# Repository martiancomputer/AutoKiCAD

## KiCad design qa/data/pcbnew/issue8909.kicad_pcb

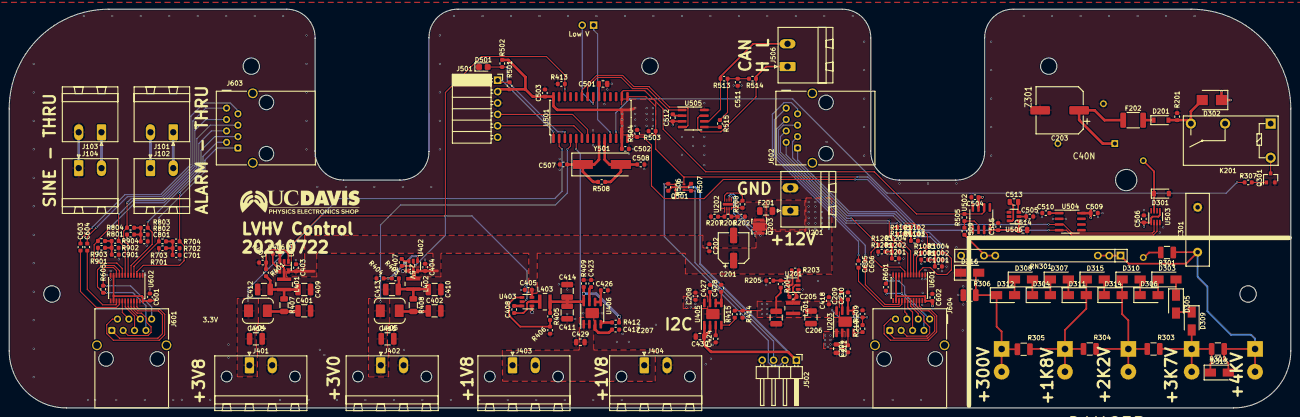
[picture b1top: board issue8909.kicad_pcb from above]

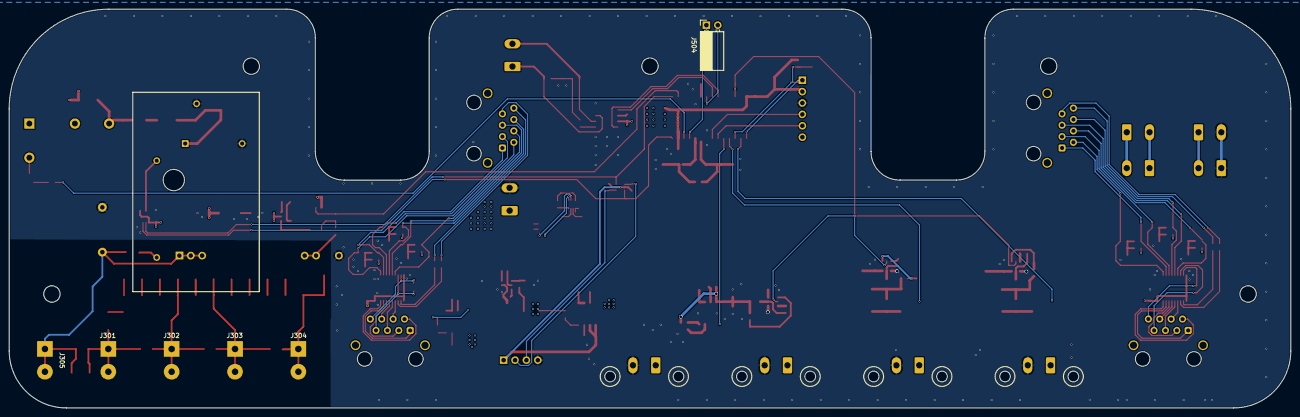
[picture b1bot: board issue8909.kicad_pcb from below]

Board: 4 copper layers, 285.8 x 88.9 mm, 204 parts (7 on the bottom side), 138 nets.

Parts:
C201: 10uF; CP_Elec_6.3x5.9
C202, C205, C208, C403, C404, C405, C406, C407, C408, C418, C502, C503, C504, C505, C506, C509, C510, C511, C512, C515, C601, C602, C603, C604, C605, C606, C701, C801, C901, C1001, C1101, C1201: 0u1F; C_0603_1608Metric
C203: 150uF; CP_Elec_10x7.7
C204, C209, C210, C417, C423, C424, C426, C427, C428: 1uF; C_0603_1608Metric
C206, C207, C409, C410, C411, C412, C413, C414: 22uF; C_1210_3225Metric
C211, C429, C430, C501, C513, C514: 10uF; C_0805_2012Metric
C301: 2nF; C_Disc_D16.0mm_W5.0mm_P10.00mm
C401, C402, C415, C416: 47uF; C_1210_3225Metric
C507, C508: 20pF; C_0603_1608Metric
D201, D301: 1N5819; D_SOD-123
D302: S1KB-13-F; D_SMB
D303, D304, D305, D306, D307, D308, D309, D310, D311, D312: 200V; D_SMA
D313, D314, D315, D316: 75V; D_SMA
D501: D_Photo; D_0805_2012Metric_Castellated
Davis_Shop_25mm: LOGO***; Davis_Shop_25mm
F201: Fuse; Fuse_1206_3216Metric
F202: Polyfuse; Fuse_1812_4532Metric_Pad1.30x3.40mm_HandSolder
J101, J102, J103, J104, J201: Conn_01x02_Male; PhoenixContact_MSTBA_2,5_2-G-5,08_1x02_P5.08mm_Horizontal
J301, J302, J303, J304, J305: Conn_01x01_Male; TE_63951-1_1x02_P5.08mm_Drill1.45mm
J401, J402, J403, J404: Conn_01x03; PhoenixContact_MSTB_2,5_2-GF-5,08_1x02_P5.08mm_Horizontal_T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
J501: Conn_01x06_Female; PinSocket_1x06_P2.54mm_Horizontal
J502: 61900419521; PinHeader_1x04_P2.54mm_Horizontal
J504: Conn_01x04; PinSocket_1x02_P2.54mm_Horizontal
J506: Conn_01x02; PhoenixContact_MSTBA_2,5_2-G-5,08_1x02_P5.08mm_Horizontal
J601, J602, J603, J604: RJ45; RJ45_Wuerth_615008142621_Horizontal
K201: G5Q-1A4 DC12; Relay_SPST_Omron-G5Q-1A
L201, L401, L402, L403: 3u3H; L_Pulse_PA4331.332NLT
L404, L405: 200nH; L_Bourns_SRP5015
Q203: CSD87312Q3E; Texas_CSD87312Q3E
Q301: MMBTA42; SOT-23
Q501: DMN601DWK-7; SOT-363_SC-70-6
R201, R203, R208, R209, R210, R409, R412, R414, R415: 100k; R_0603_1608Metric
R202: 1M33; R_0603_1608Metric
R204: 54k9; C_0603_1608Metric
R205, R402, R404, R406, R413, R501, R502, R505, R509, R701, R801, R901, R1001, R1101, R1201: 10k; R_0603_1608Metric
R206: 20k; R_0603_1608Metric
R207: 42k; R_0603_1608Metric
R301: 100R; R_1210_3225Metric
R302, R304, R306: 2M; R_1210_3225Metric
R303, R305: 10M; R_1210_3225Metric
R307: 1k; R_0603_1608Metric
R401: 39k; C_0603_1608Metric
R403: 29k; C_0603_1608Metric
R405: 24k9; R_0603_1608Metric
R407, R408: 0R2; R_1206_3216Metric
R503, R504, R506, R507: 2k; R_0603_1608Metric
R508: 1M; R_0603_1608Metric
R513, R514: 60R4; C_0603_1608Metric
R515: 300R; C_0603_1608Metric
R601, R605: 100R; R_0603_1608Metric
R702, R802, R902, R1002, R1102, R1202: 5k7; R_0603_1608Metric
R703, R704, R803, R804, R903, R904, R1003, R1004, R1103, R1104, R1203, R1204: 49R9; R_0603_1608Metric
RN301: HVD5-A50M; Caddock_USVD_HVD
U201, U401, U402, U403: TPS562200; SOT-23-6
U202: LTC4365IDDB; DFN-8-1EP_2x3mm_P0.5mm_EP0.61x2.2mm
U203, U405: ADP7158ARDZ-3.3; SOIC-8-1EP_3.9x4.9mm_P1.27mm_EP2.29x3mm
U406: ADP7158ARDZ-1.8; SOIC-8-1EP_3.9x4.9mm_P1.27mm_EP2.29x3mm
U501: DSPIC33EV256GM102; SOIC-28W_7.5x17.9mm_P1.27mm
U502: OPA196IDR; SOIC-8_3.9x4.9mm_P1.27mm
U503: LTC2631-HZ; TSOT-23-8
U504: HIH6030-21; SOIC-8_3.9x4.9mm_P1.27mm
U505: MCP2561-E-SN; SOIC-8_3.9x4.9mm_P1.27mm
U506: ADM8828; SOT-23-6
U601, U602: FIN1104; TSSOP-24_4.4x7.8mm_P0.65mm
Y501: Crystal; Crystal_SMD_HC49-SD
Z301: C40N; EMCO_C40N.fp

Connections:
+3V3: C430.1, J502.1, Q501.2 (G), Q501.5 (G), R506.2, R507.2, U405.1 (VOUT), U405.2 (VOUT_SENSE)
+3V3I: C211.1, C601.2, C602.2, R701.1, R801.1, R901.1, R1001.1, R1101.1, R1201.1, U203.1 (VOUT), U203.2 (VOUT_SENSE), U601.11 (EN), U601.14 (VCC), U601.24 (VCC), U602.11 (EN), U602.14 (VCC), U602.24 (VCC)
+3V8: C409.1, C412.1, L401.2, R401.1, R407.1
+5V: C206.1, C207.1, C208.1, C418.1, C502.1, C503.1, C504.1, C505.1, C506.1, C509.1, C512.1, J501.2, L201.2, R204.1, R209.1, R210.2, R414.1, R415.2, R501.1, R502.2, R503.2, R504.2, U203.8 (VIN), U405.8 (VIN), U501.13 (VDD), U501.28 (AVDD), U502.7 (V+), U503.1 (CA1/REF_SEL), U503.5 (VCC), U504.8 (VDD), U505.3 (VDD), U506.2 (V+)
+12V: C201.1, C202.1, C403.1, C404.1, C405.1, D302.1 (K), K201.1, K201.2, Q203.6 (D), Q203.7 (D), Q203.8 (D), R203.2, U201.3 (VIN), U202.6 (Vout), U401.3 (VIN), U402.3 (VIN), U403.3 (VIN)
-5V: C514.1, C515.1, U502.4 (V-), U506.1 (VOUT)
/Alarm1: J101.1, J102.2
/Alarm2: J101.2, J102.1
/HighVoltage/HV_Ctrl: D301.1 (K), U503.7 (OUTA), Z301.3 (PrgmV)
/HighVoltage/HV_MON: R509.2, RN301.2
/HighVoltage/HV_ON_OFF: R307.1, U501.12 (SOSCO/T1CK/CN0/PMA1/RA4)
/HighVoltage/SW1: K201.5, Q301.3 (C)
/LVDSConnections/BiasNet1/in_n: J603.6, R804.2, U602.6 (RI-)
/LVDSConnections/BiasNet1/in_p: J603.3, R803.1, U602.5 (RI+)
/LVDSConnections/BiasNet2/in_n: J603.5, R904.2, U602.7 (RI-)
/LVDSConnections/BiasNet2/in_p: J603.4, R903.1, U602.8 (RI+)
/LVDSConnections/BiasNet3/in_n: J602.2, R1004.2, U601.3 (RI-)
/LVDSConnections/BiasNet3/in_p: J602.1, R1003.1, U601.4 (RI+)
/LVDSConnections/BiasNet4/in_n: J602.6, R1104.2, U601.6 (RI-)
/LVDSConnections/BiasNet4/in_p: J602.3, R1103.1, U601.5 (RI+)
/LVDSConnections/BiasNet5/in_n: J602.5, R1204.2, U601.7 (RI-)
/LVDSConnections/BiasNet5/in_p: J602.4, R1203.1, U601.8 (RI+)
/LVDSConnections/BiasNet/in_n: J603.2, R704.2, U602.3 (RI-)
/LVDSConnections/BiasNet/in_p: J603.1, R703.1, U602.4 (RI+)
/LowVoltage/1V8_OUT: C429.1, J403.1, J404.1, U406.1 (VOUT), U406.2 (VOUT_SENSE), U501.5 (PGEC1/AN3/C2IN+/RP1/CN5/RB1)
/LowVoltage/2V6: C411.1, C414.1, L403.2, R405.1, R409.1, R412.2, U406.8 (VIN)
/LowVoltage/2V6_Feedback: R405.2, R406.1, U403.4 (VFB)
/LowVoltage/3V0: C410.1, C413.1, L402.2, R403.1, R408.1
/LowVoltage/3V0_Feedback: R403.2, R404.1, U402.4 (VFB)
/LowVoltage/3V0_OUT: C416.1, J402.1, L405.2, U501.4 (PGED1/AN2/C2IN-/RP0/CN4/RB0)
/LowVoltage/3V8_Feedback: R401.2, R402.1, U401.4 (VFB)
/LowVoltage/3V8_OUT: C415.1, J401.1, L404.2, U501.2 (AN0/VREF+/CN2/RA0)
/LowVoltage/LV_EN: R413.1, U401.5 (EN), U402.5 (EN), U403.5 (EN), U501.26 (PWM1L1/RP15/CN11/PMCS1/RB15)
/MCU/CAN_H: J506.1, R514.1, U505.7 (CANH)
/MCU/CAN_L: J506.2, R513.2, U505.6 (CANL)
/MCU/CAN_RX: U501.23 (PWM1H2/RP12/CN14/PMD0/RB12), U505.4 (RXD)
/MCU/CAN_TX: U501.22 (PGEC2/TMS/PWM1L3/RP11/CN15/PMD1/RB11), U505.1 (TXD)
/MCU/PGC: J501.5, U501.6 (AN4/C1IN-/RP2/CN6/RB2)
/MCU/PGD: J501.4, U501.7 (AN5/C1IN+/RP3/CN7/RB3)
/MCU/SCL: Q501.3 (D), R503.1, U501.15 (PGEC3/ASCL1/RP6/CN24/PMD6/RB6), U503.2 (SCL), U504.3 (SCL)
/MCU/SDA: Q501.6 (D), R504.1, U501.14 (PGED3/ASDA1/RP5/CN27/PMD7/RB5), U503.3 (SDA), U504.4 (SDA)
/PowerInput/5V_Feedback: R204.2, R205.1, U201.4 (VFB)
/PowerInput/VIN: F201.2, J201.1
/PowerInput/VIN_FUSED: F201.1, Q203.1 (D), Q203.2 (D), Q203.3 (D), Q203.4 (D), R202.1, R208.1, U202.4 (Vin)
/Sine: J103.1, J104.2
GND: C201.2, C202.2, C203.2, C204.1, C206.2, C207.2, C208.2, C209.2, C210.2, C211.2, C301.2, C401.2, C402.2, C403.2, C404.2, C405.2, C409.2, C410.2, C411.2, C412.2, C413.2, C414.2, C415.2, C416.2, C417.1, C418.2, C423.2, C424.1, C426.2, C427.2, C428.2, C429.2, C430.2, C501.2, C502.2, C503.2, C504.2, C505.2, C506.2, C507.2, C508.2, C509.2, C510.2, C511.2, C512.2, C514.2, C515.2, C601.1, C602.1, C701.2, C801.2, C901.2, C1001.2, C1101.2, C1201.2, D301.2 (A), D316.1 (K), D501.1 (K), J103.2, J104.1, J201.2, J401.2, J402.2, J403.2, J404.2, J501.3, J502.4, Q301.2 (E), R201.2, R205.2, R207.2, R209.2, R306.2, R402.2, R404.2, R406.2, R409.2, R413.2, R414.2, R702.2, R802.2, R902.2, R1002.2, R1102.2, R1202.2, RN301.3, U201.1 (GND), U202.1 (GND), U202.9 (GND), U203.9 (GND), U401.1 (GND), U402.1 (GND), U403.1 (GND), U405.9 (GND), U406.9 (GND), U501.8 (VSS), U501.19 (VSS), U501.27 (AVSS), U502.3 (+), U503.4 (GND), U504.2 (GND), U505.2 (VSS), U505.8 (STBY), U506.4 (GND), U601.1 (GND), U601.2 (GND), U601.12 (GND), U601.23 (~EN), U602.1 (GND), U602.2 (GND), U602.12 (GND), U602.23 (~EN), Z301.2 (GND), Z301.5 (CASE)
unnamed: C203.1, F202.1, Z301.1 (P_IN)
unnamed: C204.2, U203.3 (BYP)
unnamed: C205.1, L201.1, U201.2 (SW)
unnamed: C205.2, U201.6 (VBST)
unnamed: C209.1, U203.7 (VREG)
unnamed: C210.1, U203.5 (REF_SENSE), U203.6 (REF)
unnamed: C301.1, D313.2 (A), J305.1, R301.1, R302.1, RN301.1
unnamed: C401.1, L404.1, R407.2
unnamed: C402.1, L405.1, R408.2
unnamed: C406.1, L401.1, U401.2 (SW)
unnamed: C406.2, U401.6 (VBST)
unnamed: C407.1, L402.1, U402.2 (SW)
unnamed: C407.2, U402.6 (VBST)
unnamed: C408.1, L403.1, U403.2 (SW)
unnamed: C408.2, U403.6 (VBST)
unnamed: C417.2, U406.3 (BYP)
unnamed: C423.1, U406.7 (VREG)
unnamed: C424.2, U405.3 (BYP)
unnamed: C426.1, U406.5 (REF_SENSE), U406.6 (REF)
unnamed: C427.1, U405.7 (VREG)
unnamed: C428.1, U405.5 (REF_SENSE), U405.6 (REF)
unnamed: C501.1, U501.20 (VCAP)
unnamed: C507.1, R508.1, U501.9 (OSC1/CLKI/CN30/RA2), Y501.1
unnamed: C508.1, R508.2, U501.10 (OSC2/CLKO/CN29/PMA0/RA3), Y501.2
unnamed: C510.1, U504.1 (VCORE)
unnamed: C511.1, R513.1, R514.2, R515.1
unnamed: C513.1, U506.6 (CAP+)
unnamed: C513.2, U506.3 (CAP-)
unnamed: C603.1, J603.7
unnamed: C603.2, U602.16 (DO+)
unnamed: C604.1, J603.8
unnamed: C604.2, U602.15 (DO-)
unnamed: C605.1, J602.7
unnamed: C605.2, U601.16 (DO+)
unnamed: C606.1, J602.8
unnamed: C606.2, U601.15 (DO-)
unnamed: C701.1, R701.2, R702.1, R703.2, R704.1
unnamed: C801.1, R801.2, R802.1, R803.2, R804.1
unnamed: C901.1, R901.2, R902.1, R903.2, R904.1
unnamed: C1001.1, R1001.2, R1002.1, R1003.2, R1004.1
unnamed: C1101.1, R1101.2, R1102.1, R1103.2, R1104.1
unnamed: C1201.1, R1201.2, R1202.1, R1203.2, R1204.1
unnamed: D201.1 (K), F202.2
unnamed: D201.2 (A), D302.2 (A), K201.3, R201.1
unnamed: D303.1 (K), D306.2 (A)
unnamed: D303.2 (A), D305.1 (K)
unnamed: D304.1 (K), D308.2 (A)
unnamed: D304.2 (A), D307.1 (K)
unnamed: D305.2 (A), D309.1 (K)
unnamed: D306.1 (K), D310.2 (A)
unnamed: D307.2 (A), D311.1 (K)
unnamed: D308.1 (K), D312.2 (A)
unnamed: D309.2 (A), D313.1 (K), J301.1, R302.2, R303.1
unnamed: D310.1 (K), D314.2 (A), J302.1, R303.2, R304.1
unnamed: D311.2 (A), D315.1 (K), J303.1, R304.2, R305.1
unnamed: D312.1 (K), D316.2 (A), J304.1, R305.2, R306.1
unnamed: D314.1 (K), D315.2 (A)
unnamed: D501.2 (A), R502.1, U501.3 (AN1/VREF-/CN3/RA1)
unnamed: J501.1, R501.2, U501.1 (~MCLR)
unnamed: J502.2, Q501.4 (S), R506.1
unnamed: J502.3, Q501.1 (S), R507.1
unnamed: J504.1, U501.11 (SOSCI/RP4/CN1/PMBE/RB4)
unnamed: J504.2, U501.21 (PGED2/TDI/PWM1H3/RP10/CN16/PMD2/RB10)
unnamed: J601.1, U602.21 (DO+)
unnamed: J601.2, U602.22 (DO-)
unnamed: J601.3, U602.20 (DO+)
unnamed: J601.4, U602.17 (DO+)
unnamed: J601.5, U602.18 (DO-)
unnamed: J601.6, U602.19 (DO-)
unnamed: J601.7, R605.1, U602.9 (RI+)
unnamed: J601.8, R605.2, U602.10 (RI-)
unnamed: J604.1, U601.21 (DO+)
unnamed: J604.2, U601.22 (DO-)
unnamed: J604.3, U601.20 (DO+)
unnamed: J604.4, U601.17 (DO+)
unnamed: J604.5, U601.18 (DO-)
unnamed: J604.6, U601.19 (DO-)
unnamed: J604.7, R601.1, U601.9 (RI+)
unnamed: J604.8, R601.2, U601.10 (RI-)
unnamed: Q203.5 (G), U202.5 (GATE)
unnamed: Q301.1 (B), R307.2
unnamed: R202.2, R206.1, U202.3 (UV)
unnamed: R203.1, U201.5 (EN)
unnamed: R206.2, R207.1, U202.2 (OV)
unnamed: R208.2, U202.8 (~SHDN)
unnamed: R210.1, U203.4 (EN)
unnamed: R301.2, Z301.4 (HV_Out)
unnamed: R412.1, U406.4 (EN)
unnamed: R415.1, U405.4 (EN)
unnamed: R505.1, U501.16 (INT0/RP7/CN23/PMD5/RB7), U502.6
unnamed: R505.2, R509.1, U502.2 (-)
unnamed: R515.2, U505.5 (SPLIT)
